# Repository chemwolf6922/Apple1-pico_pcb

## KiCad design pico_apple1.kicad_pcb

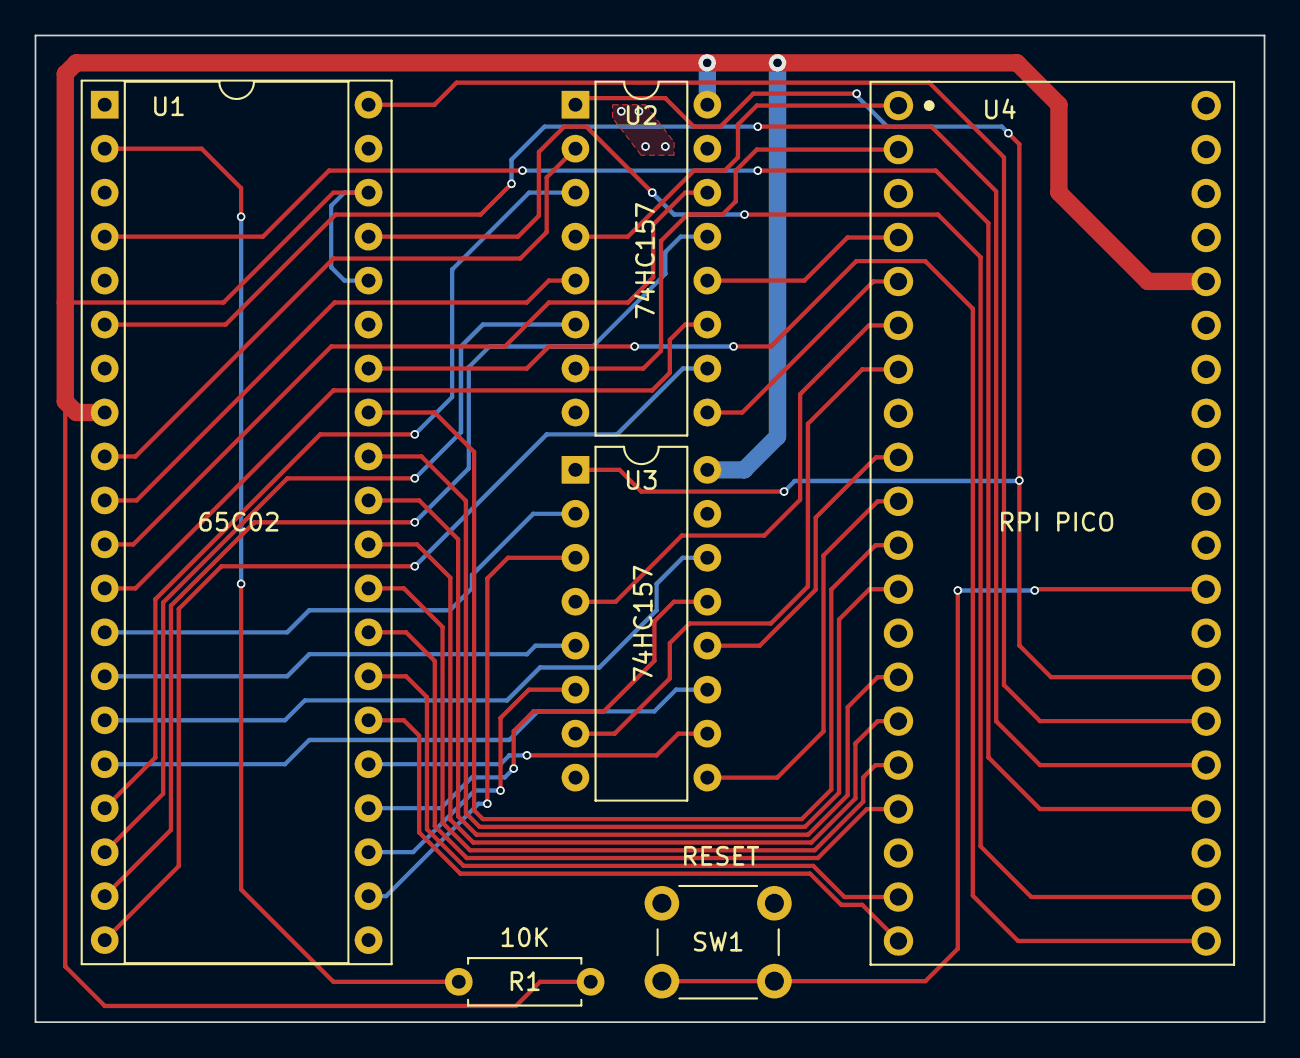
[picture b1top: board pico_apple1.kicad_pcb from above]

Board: 2 copper layers, 71.0 x 57.0 mm, 6 parts (0 on the bottom side), 42 nets.

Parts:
R1: 10k; R_Axial_DIN0207_L6.3mm_D2.5mm_P7.62mm_Horizontal
SW1: SW_Push; SW_PUSH_6mm_H5mm
U1: 65C02; DIP-40_W15.24mm_Socket
U2, U3: 74LS157; DIP-16_W7.62mm
U4: pi_pico

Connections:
+3V3: R1.2, U1.8 (VDD), U1.36 (BE), U1.38 (SOB), U2.16 (VCC), U3.16 (VCC), U4.36 (3V3(OUT))
/AS: U2.1 (S), U3.1 (S), U4.27 (GP21)
/CLK: U1.37 (PHI2), U4.22 (GP17)
/R/W: U1.34 (RWB), U4.21 (GP16)
/~IRQ: U1.4 (IRQB), U4.24 (GP18)
/~NMI: U1.6 (NMIB), U4.25 (GP19)
/~RST: U1.40 (RESB), U4.26 (GP20)
GND: SW1.1, U1.21 (VSS), U2.8 (GND), U2.15 (E), U3.8 (GND), U3.15 (E), U4.3 (GND), U4.8 (GND), U4.13 (GND), U4.18 (GND), U4.23 (GND), U4.28 (GND), U4.33 (GND), U4.38 (GND)
unnamed: R1.1, U1.2 (RDY)
unnamed: U1.9 (A0), U2.2 (I0a)
unnamed: U1.10 (A1), U2.5 (I0b)
unnamed: U1.13 (A4), U3.2 (I0a)
unnamed: U1.14 (A5), U3.5 (I0b)
unnamed: U1.17 (A8), U2.3 (I1a)
unnamed: U1.18 (A9), U2.6 (I1b)
unnamed: U1.22 (A12), U3.3 (I1a)
unnamed: U1.23 (A13), U3.6 (I1b)
unnamed: U1.24 (A14), U3.13 (I1d)
unnamed: U1.26 (D7), U4.20 (GP15)
unnamed: U1.27 (D6), U4.19 (GP14)
unnamed: U1.28 (D5), U4.17 (GP13)
unnamed: U1.29 (D4), U4.16 (GP12)
unnamed: U1.30 (D3), U4.15 (GP11)
unnamed: U1.31 (D2), U4.14 (GP10)
unnamed: U1.32 (D1), U4.12 (GP9)
unnamed: U1.33 (D0), U4.11 (GP8)
unnamed: U2.4 (Za), U4.1 (GP0)
unnamed: U2.7 (Zb), U4.2 (GP1)
unnamed: U2.9 (Zc), U4.5 (GP3)
unnamed: U1.20 (A11), U2.10 (I1c)
unnamed: U1.12 (A3), U2.11 (I0c)
unnamed: U2.12 (Zd), U4.4 (GP2)
unnamed: U1.19 (A10), U2.13 (I1d)
unnamed: U1.11 (A2), U2.14 (I0d)
unnamed: U3.4 (Za), U4.6 (GP4)
unnamed: U3.7 (Zb), U4.7 (GP5)
unnamed: U3.9 (Zc), U4.10 (GP7)
unnamed: U1.25 (A15), U3.10 (I1c)
unnamed: U1.16 (A7), U3.11 (I0c)
unnamed: U3.12 (Zd), U4.9 (GP6)
unnamed: U1.15 (A6), U3.14 (I0d)
unnamed: SW1.2, U4.29 (GP22)

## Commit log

2022-11-12 init
